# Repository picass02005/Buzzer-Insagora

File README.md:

# General description

This project is a request from Insagora club, realised in associon with Club Robot and Club Info.

It consists of a set of buzzers (ESP-32 based) communicating with a PC backend and a web frontend.

# Contacts

Club Info: <[club.info@amicale-insat.fr](mailto:club.info@amicale-insat.fr)><br>
Club Robot: <[club.robot@amicale-insat.fr](mailto:club.robot@amicale-insat.fr)>

Main developper: Clément Duran <[clementduran0@gmail.com](mailto:clementduran0@gmail.com)>

# Manual

## Software installation

### From pre-compiled code

A GitHub action is set up to compile the code on every push on `master`.

To download it:

1. Go to [actions](https://github.com/picass02005/Buzzer-Insagora/actions) tab
2. Select the last run
3. You can download an executable from artifacts (one for Windows, one for Linux)

> [!NOTE] Antivirus
> For an unknown reason, on Windows, sometimes Windows defender will block the execution.
> You can force it on the popup that will appear.

### From source code

#### Clone this project

To clone this project, you can use the following :

```bash
git clone https://github.com/picass02005/Buzzer-Insagora.git
```

#### Create a virtualenv (recommended)

To execute this code cleanly, I recommend you to create a virtualenv.
You can do this by running the following command on this project root (where this README is located):

```bash
python3 -m venv .venv
```

Then you need to load your venv environment:

```bash
# On linux
source .venv/bin/activate

# On windows
.venv\Scripts\activate.bat
```

#### Install depedencies

To install depedencies, you must run the following:

```bash
python3 -m pip -r requirements.txt
```

#### Run the program

Finally, you can run the program (you need to be at the root of this project):

```bash
python3 backend/main.py
```

#### Compile from sources

If you want to compile your own binaries, you need to install [PyInstaller](https://pyinstaller.org/en/stable/):

```bash
# This may depends on your operating system, please refer to PyInstaller documentation
python3 -m pip install pyinstaller
```

You can now compile your binary using:

```bass
make exe_win    # You must be on Windows to run this
make exe_linux  # You must be on linux to run this
```

The executable will be in `./dist`.

If needed, you have serveral tools in this project `Makefile` that you can use to compile or upload the onboard code for
ESP32 boards. Those tools uses `arduino-cli` and were tested on Linux. You can also upload it using Arduino IDE.

# Technical specifications

## Hardware

### Electronic

All files related to PCB conceptions can be found under [CAO/PCB](./CAO/PCB).

You can ask GEI for custom PCB. You need to give them the files under [pdf_mask](./CAO/PCB/pdf_mask/).

If needed, the kicad project can be found under [kicad_project](./CAO/PCB/kicad_project/).

### Casing

The casing was made using onshape. Its project can be found under [this link](https://cad.onshape.com/documents/d32b5483efb85fc275e8530b/w/3e110ba059403e44c50f27c8/e/61eb53e4b49d77882c064105?renderMode=0&uiState=69906051c49d80537d0f6ebd).

You can find all STL files necessary to 3D print it under [3D-model-str](./CAO/3D-model-stl/).

## Software

### Communication diagram

```mermaid
flowchart LR
    A[Computer] <-->|Bluetooth Low Energy| B[Buzzer-1<br>&quot;Gateway&quot;]
    subgraph Buzzer network
        B <-->|ESP-Now| C[Buzzer-2]
        B <-->|ESP-Now| D[Buzzer-3]
        B <-->|ESP-Now| E[...]
    end
```

### Computer to gateway communication

All packets sent from the computer follow the same general PDU:

```mermaid
packet
0-6: "Destination adress"
7: "ID"
8-31: "Command (separated from data by a space, variable length)"
32-63: "Data (Optional, variable length)"
64-95: "Padding (Optional, total length is 240 bytes)"
```

Data are raw bytes.
Broadcast address is `\xFF\xFF\xFF\xFF\xFF\xFF` (or more human-readable `ff:ff:ff:ff:ff:ff`).

ID refers to a command ID, used for polling responses in backend.

### Gateway to computer communication

Communication from gateway to computer isn't totally normalized.

```mermaid
packet
0: "ID"
1-31: "Data (not normalized, variable length)"
```

Max data size is 240 bytes.

It is made from `data` field of a `ESPNowMessage` where `fwd_ble` is `1`.

### Between multiple ESP

All packets through the ESP-NOW network are currently sent to broadcast address (`ff:ff:ff:ff:ff:ff`).

Each of them is a `ESPNowMessage`.

Structure of `ESPNowMessage`:

- `char fwd_ble`: Represent if the message should be forwarded through BLE network when it reaches the gateway.<br>
  To forward it, set its value to `1`, else set it to `0`.
- `char target[6]`: Contain the target ESP MAC address for this packet.<br>
  Set it to `{0xff, 0xff, 0xff, 0xff, 0xff, 0xff}` for a broadcast message.<br>
  For this purpose, you can use the `broadcastAddress` constant.
- `char data[240]`: The raw data of this packet.<br>
  If you're sending a command and its data, separate them with a space.

### Example communication

In the following example, we suppose we have a generic `PING` command where respond is in the form
`PONG [destination MAC address]`.

#### Example 1: direct command to gateway

```mermaid
sequenceDiagram
    participant C as Computer
    box Grey ESP-NOW network
        participant G as Buzzer 1 (Gateway)<br>aa:aa:aa:aa:aa:aa
        participant B2 as Buzzer 2<br>bb:bb:bb:bb:bb:bb
        participant B3 as Buzzer 3<br>cc:cc:cc:cc:cc:cc
    end

    C->>G: Target: aa:aa:aa:aa:aa:aa<br>Data: PING
    activate G
    G->>C: Data: PONG aa:aa:aa:aa:aa:aa
    deactivate G
```

#### Example 2: command to a specific buzzer

```mermaid
sequenceDiagram
    participant C as Computer
    box Grey ESP-NOW network
        participant G as Buzzer 1 (Gateway)<br>aa:aa:aa:aa:aa:aa
        participant B2 as Buzzer 2<br>bb:bb:bb:bb:bb:bb
        participant B3 as Buzzer 3<br>cc:cc:cc:cc:cc:cc
    end

    C->>G: Target: bb:bb:bb:bb:bb:bb<br>Data: PING
    G->>B2: Target: bb:bb:bb:bb:bb:bb<br>Data: PING<br>Fwd_ble: 0
    activate B2
    B2->>G: Target: aa:aa:aa:aa:aa:aa<br>Data: PONG bb:bb:bb:bb:bb:bb<br>Fwd_ble: 1
    deactivate B2
    G->>C: Data: PONG bb:bb:bb:bb:bb:bb
```

#### Example 3: command to every buzzers

```mermaid
sequenceDiagram
    participant C as Computer
    box Grey ESP-NOW network
        participant G as Buzzer 1 (Gateway)<br>aa:aa:aa:aa:aa:aa
        participant B2 as Buzzer 2<br>bb:bb:bb:bb:bb:bb
        participant B3 as Buzzer 3<br>cc:cc:cc:cc:cc:cc
    end
    
    C->>G: Target: ff:ff:ff:ff:ff:ff<br>Data: PING
    activate G
    par BROADCASTING
        G->>C: Data: PONG aa:aa:aa:aa:aa:aa
        deactivate G
        G->>B2: Target: ff:ff:ff:ff:ff:ff<br>Data: PING<br>Fwd_ble: 0
        activate B2
        B2 ->> G: target: aa:aa:aa:aa:aa:aa<br>Data: PONG bb:bb:bb:bb:bb:bb<br>Fwd_ble: 1
        deactivate B2
        G->>C: Data: PONG bb:bb:bb:bb:bb:bb
        G->>B3: Target: ff:ff:ff:ff:ff:ff<br>Data: PING<br>Fwd_ble: 0
        activate B3
        B3 ->> G: target: aa:aa:aa:aa:aa:aa<br>Data: PONG cc:cc:cc:cc:cc:cc<br>Fwd_ble: 1
        deactivate B3
        G->>C: Data: PONG cc:cc:cc:cc:cc:cc
    end
```

### Commands

#### Ping

Command used to ping any ESP.
Response contains the target MAC address (in this example : `AA:BB:CC:DD:EE:FF`).

> Command : `PING`
> Response : `PING AA:BB:CC:DD:EE:FF`

#### Get clock

Command used to get internal clock value.
If internal clock is not set, its value will be `INT64_MAX` (9,223,372,036,854,775,807)

In this example, MAC address is `AA:BB:CC:DD:EE:FF`, its internal clock is `1234`.

> Command : `GCLK`
> Response: `GCLK AA:BB:CC:DD:EE:FF 1234`

#### Reset clock

Reset an ESP internal clock.

For the master, default value is `0`.
For another ESP, default value is `INT64_MAX` (9,223,372,036,854,775,807).

This command does not send any response.

> Command: `RCLK`

#### Set clock

Command used to set internal clock.
This command does not send any response.

The internal clock is only set if new clock value is less than actual clock value.

In this example, we set the internal clock to `1234`.

> Command: `SCLK 1234`

#### Automatic set clock

Command used to delegate the set clock procedure to the master ESP.
This will execute the following commands:

1. `RCLK` (broadcast)
2. `SCLK actual_clock` (broadcast, actual_clock being the clock of master)

The `SCLK` is repeated a number of time defined by `AUTO_SET_CLK_NB` in `cmd-clock.cpp`.

> Command: `ACLK`
> Response: `ACLK success`

#### Get LED number

This command return the number of LED installed on a buzzer.

In this example, we suppose the buzzer have 8 LEDs.

> Command: `GLED`
> Response: `GLED 8`

#### Set LED

This command set the LEDs color on a buzzer.
This command does not send any response.

Each LED color is represented on 3 bytes in raw value.

Its PDU is defined as following:

```mermaid
packet
0-5: "SLED [space]"
6: "R_1"
7: "G_1"
8: "B_1"
9: "R_2"
10: "G_2"
11: "B_2"
12-31: "Other LED color (variable length)"
```

For the next example, there is a quick reminder from extended ASCII codes:

```
ASCII -> DEC | HEX
!     -> 33  | 0x21
ÿ     -> 255 | 0xff
```

In this example, I have a buzzer with 3 LED, and I want to set them to `0xFF2121`, `0x21FF21` and `0x2121FF`. This
translate into `ÿ!!`, `!ÿ!` and `!!ÿ`.

> Command: `SLED ÿ!!!ÿ!!!ÿ`

#### Clear LED

This command turn off all LEDs on a buzzer.
This command does not send any response.

> Command: `CLED`

### On board

#### Which callback to use for communication?

For every communication (from master buzzer or other buzzers), send messages using `esp_now_send_message` (defined in
`esp-now.h`).

#### How to add a command?

If you want to add commands, you need to define a callback with this signature:

```cpp
void MyAwesomeCommand(ESPNowMessage message);
```

The message passed is the original message.
You then need to add it in `commands_handler` (`commands_handler.h`).

### Backend

The backend is defined in 2 different stack:

- Communication stack
- API stack

Communication stack is responsible for the BLE communication between the PC and master buzzer.
You can find it under `./backend/ESPCommunication`.

API stack is a layer for communicating with BLE stack. It also implements teams, LED management and flow control.
You can find it under `./GUI/API`.

Every function have a full docstring you can refer to for more informations.

### API

All API calls are defined under `http://your_hostname/api`.

#### /api/status/get_connected [GET]

Return a JSON containing connected buzzers MAC address.
By default, it uses a cache value (if valid) to reduce ping.
You can force to repopulate cache by using `/api/status/get_connected?no_cache=true`.

No parameters are set in body.

Example response:

```JSON
{
    "connected": [
        "AA:AA:AA:AA:AA:AA",
        "BB:BB:BB:BB:BB:BB"
    ]
}
```

#### /api/status/get_state [GET]

Return the current flow state of the buzzers.

Valid states are:

- `IDLE`: The buzzer system is waiting for an operation. Its LED show current team points.
- `WAIT`: The buzzer system is waiting for a button press. Its LED are set to white.<br>
  When a press is registered, next state is `CHECK`.
- `CHECK`: The buzzer system is waiting for a confirmation or a denial from the game master. When waiting for
  confirmation, LEDs are green and red.<br>
  When answer is confirmed, a quick animation shows and state is set to `IDLE`.

No parameters are set in body.

Example response:

```JSON
{
    "state": "IDLE"
}
```

#### /api/flow/wait_press [POST]

Executes the following:

1. Reset master buzzer clock
2. Auto-synchronize all buzzers clock (`ACLK`)
3. Change game state to `WAIT` (+ change LED accordingly)
4. Wait for a button press event
5. Wait a few millisecond and detect the first press (regarding clock)
6. Change game state to `CHECK` (+ change LED accordingly)

No parameters are set in body.

This method return a partial file for each game state changes.

When going to `WAIT` state:

```JSON
{
    "state": "waiting for press"
}
```

When going to `CHECK` state:

```JSON
{
    "state": "waiting for confirmation"
}
```

#### /api/flow/confirm [POST]

This method must be called when in `CHECK` state to confirm a participant answer.

This makes the LED blink briefly in green and add a point to this buzzer's team.
After this method, game state go into `IDLE`.

No parameters are set in body.

This returns a JSON containing status / error like this:

```JSON
{
    "status": "ok"
}
```

#### /api/flow/deny [POST]

This method must be called when in `CHECK` state to not confirm a participant answer.

This makes the LED blink briefly in red.
After this method, game state go into `IDLE`.

No parameters are set in body.

This returns a JSON containing status / error like this:

```JSON
{
    "status": "ok"
}
```

#### /api/teams/get [GET]

This method is used to get all teams information.

No parameters are set in body.

An example return is like this:

```JSON
{
    "test_1": {
        "associated_buzzers": [
            "AA:AA:AA:AA:AA:AA"
        ],
        "name": "test_1",
        "point": 0,
        "point_limit": 8,
        "primary_color": "FF0000",
        "secondary_color": "FFFF00"
    },
    "test_2": {
        "associated_buzzers": [
            "BB:BB:BB:BB:BB:BB"
        ],
        "name": "test_2",
        "point": 0,
        "point_limit": 8,
        "primary_color": "0000FF",
        "secondary_color": "8000FF"
    }
}
```

#### /api/teams/make [POST]

This method is used to make a new team.

Your call must have the following body fields:

```JSON
{
    "team_name": "test_1",
    "primary_color": "#ff0000",
    "secondary_color": "#ffff00"
}
```

Primary color refers to the color of the team.
Secondary color is used to display points when limit is greater than 8.

This returns a JSON containing status / error like this:

```JSON
{
    "status": "ok"
}
```

#### /api/teams/delete [DELETE]

This method deletes a team.

Your call must have the following body fields:

```JSON
{
    "team_name": "test_1"
}
```

This returns a JSON containing status / error like this:

```JSON
{
    "status": "ok"
}
```

#### /api/teams/set_point_limit [PATCH]

This method set a new point limit for all teams.

After calling this method, you should reset point number.

Your call must have the following body fields:

```JSON
{
    "limit": 10
}
```

This returns a JSON containing status / error like this:

```JSON
{
    "status": "ok"
}
```

#### /api/teams/reset_points [PATCH]

This method reset all teams point to 0. After that, it reset LED display to default.

No parameters are set in body.

This returns a JSON containing status / error like this:

```JSON
{
    "status": "ok"
}
```

#### /api/teams/change_name [PATCH]

This method is used to change a team name.

Your call must have the following body fields:

```JSON
{
    "old_name": "test_1",
    "new_name": "t_1"
}
```

This returns a JSON containing status / error like this:

```JSON
{
    "status": "ok"
}
```

#### /api/teams/update [PATCH]

This method is used to update a team attributes.

Your call must define at least this body fields:

```JSON
{
    "team_name": "test_1"
}
```

You can add optional fields to modify this team attributes.

- `"associated_buzzers": ["AA:AA:AA:AA:AA:AA"]`: A list of all associated buzzers MAC addressù
- `"point": 0`: Set point number to the given value
- `"primary_color": "0000FF"`: Set the team primary color
- `"secondary_color": "00FF00"`: Set the secondary color

If you change `associated_buzzers`, backend will check that your buzzers are currently connected.

Example body:

```JSON
{
    "team_name": "test_1",
    "associated_buzzers": [
        "AA:AA:AA:AA:AA:AA"
    ],
    "point": 0,
    "primary_color": "0000FF",
    "secondary_color": "00FF00"
}
```

This returns a JSON containing status / error like this:

```JSON
{
    "status": "ok"
}
```

#### /api/lights/reset_led_default [PUT]

This method reset all buzzers LED to default value.

If status is `IDLE`, default value is the number of points lit up with team color.

If status is `WAIT`, default value is all LED in white.

If status is `CHECK`, default value is all buzzers off except the first one to have pressed the buzzer. Its LED are red
and green.

No parameters are set in body.

This returns a JSON containing status / error like this:

```JSON
{
    "status": "ok"
}
```

#### /api/lights/clear_leds [PUT]

This method set all buzzers LED to an off state.

Your call must have the following body fields:

```JSON
{
    "target_mac": "AA:AA:AA:AA:AA:AA"
}
```

This returns a JSON containing status / error like this:

```JSON
{
    "status": "ok"
}
```

#### /api/lights/get_led_nb [GET]

This method is used to get the number of onboard LED for every buzzers.

No parameters are set in body.

An example return is like this:

```JSON
{
    "number": 16
}
```

#### /api/lights/set_led_color [PUT]

This method is used to set LED color on a given buzzer, or every buzzer.

If no target MAC address is given, it defaults to broadcast address (`FF:FF:FF:FF:FF:FF`)

Example body:

```JSON
{
    "target_mac": "ff:ff:ff:ff:ff:ff",
    "colors": [
        "FF0000",
        "FFFF00",
        "00FF00",
        "00FFFF",
        "0000FF",
        "FF0000",
        "FFFF00",
        "00FF00",
        "00FFFF",
        "0000FF",
        "FF0000",
        "FFFF00",
        "00FF00",
        "00FFFF",
        "0000FF",
        "FF0000"
    ]
}
```

This returns a JSON containing status / error like this:

```JSON
{
    "status": "ok"
}
```

### Frontend

The frontend was vibe-coded using [Antigravity](https://antigravity.google/) with [Gemini](https://gemini.google.com/)
model.

One side project could be to code it properly, but by lack of time, I could not do it for now.

# License

This project is distribued under the MIT license.
For more information: https://opensource.org/licenses/MIT

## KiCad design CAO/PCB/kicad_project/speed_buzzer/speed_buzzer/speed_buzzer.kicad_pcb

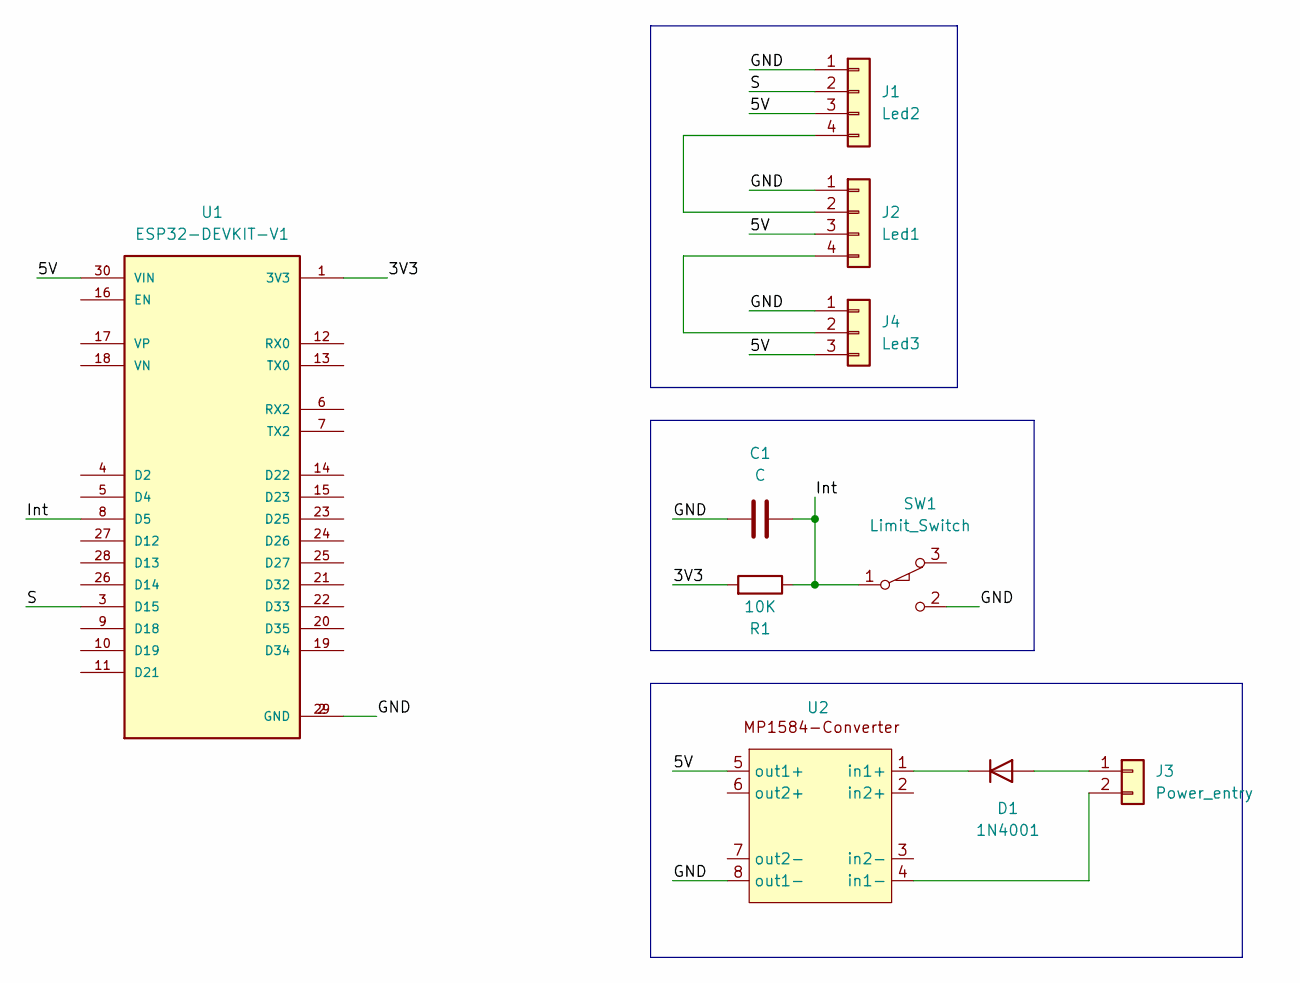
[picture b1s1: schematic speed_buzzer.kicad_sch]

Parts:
C1: C; C_Disc_D7.5mm_W2.5mm_P5.00mm
D1: 1N4001; D_DO-41_SOD81_P10.16mm_Horizontal
J1: Led2; JST_EH_B4B-EH-A_1x04_P2.50mm_Vertical
J2: Led1; JST_EH_B4B-EH-A_1x04_P2.50mm_Vertical
J3: Power_entry; JST_EH_B2B-EH-A_1x02_P2.50mm_Vertical
J4: Led3; JST_EH_B3B-EH-A_1x03_P2.50mm_Vertical
R1: 10K; R_Axial_DIN0207_L6.3mm_D2.5mm_P10.16mm_Horizontal
SW1: Limit_Switch
U1: ESP32-DEVKIT-V1; ESP32_DEVKIT_V1; PARTREV N/A
U2: mp1584

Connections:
/3V3: R1.2, U1.1 (3V3)
/5V: J1.3, J2.3, J4.3, U1.30 (VIN), U2.5 (out1+)
/GND: C1.1, J1.1, J2.1, J4.1, SW1.2 (B), U1.2 (GND), U1.29 (GND), U2.8 (out1-)
/Int: C1.2, R1.1, SW1.1 (A), U1.8 (D5)
/S: J1.2, U1.3 (D15)
unnamed: D1.2 (A), J3.1
unnamed: D1.1 (K), U2.1 (in1+)
unnamed: J1.4, J2.2
unnamed: J2.4, J4.2
unnamed: J3.2, U2.4 (in1-)

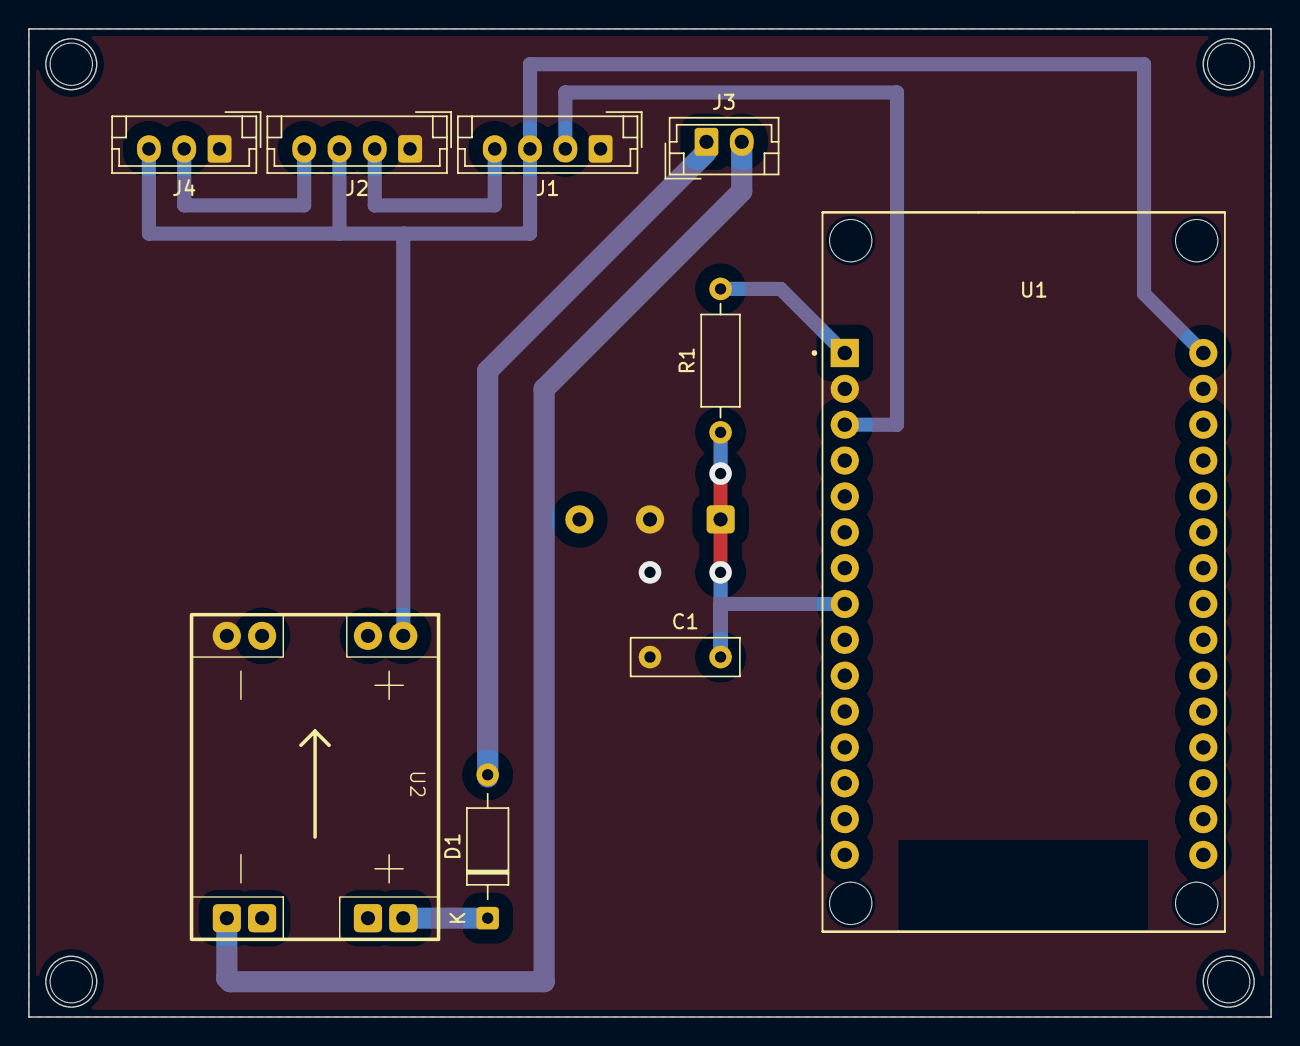
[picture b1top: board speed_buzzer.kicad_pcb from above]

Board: 2 copper layers, 88.0 x 70.0 mm, 10 parts (1 on the bottom side), 10 nets.

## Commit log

2025-11-23 Moved manual before technical specs
2025-11-23 Added license
2025-11-25 Added makefile to compile / upload ESP code
2025-11-27 Added ESP connection by BT + master detection
2025-11-28 Moved network into ble + changed BLE lib used
2025-11-28 Added esp-now connection
2025-12-04 Fixed BLE connection
2025-12-04 Added a test of ESP-NOW communication based on BLE
2025-12-05 Renamed params into data in ESP messages
2025-12-06 BLE packets are retransmissed on ESP-NOW if target != mac addr
2025-12-06 Added broadcast as valid target
2025-12-07 Added function to send BLE packets + automatic forward of BLE packets if fwd_ble=1
2025-12-07 Avoid not necessary stack copy of messages + changed data length
2025-12-07 Added generic sequence diagram to explain network
2025-12-07 Renamed BUZZERS into BUZZERS-INSAGORA
2025-12-07 Changing box to grey
2025-12-09 Added debug define to activate / desactivate serial
2025-12-09 Added command manager + PING
2025-12-11 Renamed commands into command-handler + moved ping command
2025-12-12 Added LED commands and support + fixed a bug with null bytes in BLE
2025-12-12 Changed pinout for V2 + some minor modifications with LED
2025-12-12 Minor changes
2025-12-14 Added a little LED animation over BLE
2025-12-14 Added clock managment + commands to reset, set, get and automatically set clock among clients
2025-12-15 Improved clock sync
2025-12-15 Added button interrupt
2025-12-15 Formatted every ESP files
2025-12-15 Added license headers in every files + in readme
2025-12-18 Updated readme + some commands responses
2025-12-20 Changed pin layout for prototype V3
2025-12-20 Reformated ESP code
2025-12-20 Updated gitignore
2025-12-21 Added BT communication for backend
2025-12-21 Changed data packet to include an ID for each commands
2025-12-21 Modofoed gitignore
2025-12-21 Modified readme according to new packets format
2025-12-21 Added command ID in communication
2025-12-21 WIP: ping command TODO: polling of responses
2025-12-22 Add response polling + finished ping command
2025-12-22 Updated a mermaid diagram in readme
2025-12-22 Added requirements.txt
2025-12-22 Added GCLK command + pretty format for RecvObject
2025-12-22 Added reset_clock set_clock and automatic_set_clock
2025-12-22 Added get_led_number + renamed args into data in RecvObject
2025-12-23 Added set led command, LEDs class and Color class
2025-12-23 Added clear LED command
2025-12-23 Updated TODO
2025-12-23 Add command to remove every instance of a command from polling
2025-12-23 Rewrite all docstrings using Google styling
2025-12-28 Added callback on BPRS (for now it only prints BPRS sorted by internal clock values after a short polling) + renamed "Modules" into "ESPCommunication" for later scalability
2025-12-28 Added a method to wait for a press and get only first one
2025-12-28 Using low level asyncio to run main loop forever
2025-12-28 Added GUI support + test page
2025-12-28 Added docstring + support for bt_comm in blueprints
2025-12-28 Added function to try to connect to buzzers until it's successful
2025-12-28 Added copyright + handled an exception when connecting to BLE
2026-01-04 Added majority of backend's logic
2026-01-04 Added a cache to keep a list of connected buzzers
2026-01-04 Removed some junk in main
2026-01-04 Added caching of connected buzzers + API endpoints to get status from the backend
2026-01-05 Added check API endpoint
2026-01-05 Added docstrings
2026-01-12 Added make_team endpoint + moved get_teams endpoint
2026-01-15 When ble disconnects, LEDs are reset on every ESP
2026-01-15 Added delete team
2026-01-15 Added change team name
2026-01-15 Bugfix when getting a color from hex
2026-01-15 Added update team
2026-01-15 Enhanced logic for checking if a hex value is a valid color
2026-01-15 Added docstring
2026-01-15 Added endpoint to reset LED to current state
2026-01-24 Added lights
2026-01-24 Added flow API + deleted test
2026-01-29 Modified main loop to properly propagate signals
2026-01-29 Updated README with all API doc + fixed some minor bugs
2026-01-29 Vibe coding the frontend
2026-01-29 Added a way to open main page on startup
2026-01-29 Added a default behavior when no buzzers are connected and pinging
2026-01-29 Added a refresh buzzer list button when adding / editing teams
2026-01-29 Trying to add workflow for auto build
2026-01-29 Reverting
2026-02-03 Hopefully fixed team synchronization across multiple modules
2026-02-05 Final fix
2026-02-08 Added __init__ to allow for compiling using pyinstaller + added compile commands in makefile + updated gitignore + tried github actions to compile automatically
2026-02-08 Fixed a bug in action for linux build
2026-02-08 Forgot to install pyinstaller in my action
2026-02-08 Hopefully this time is the one
2026-02-08 Updated readme + added copyright when needed
2026-02-09 Fixed makefile
2026-02-10 MAde confirm / deny animation shorter
2026-02-10 Added infinite points
2026-02-14 Trying to fix github linux build
2026-02-14 Take 2
2026-02-14 Take 3
2026-02-14 Take 4
2026-02-14 Take 5
2026-02-14 Take 6
2026-02-14 Take 7
2026-02-14 Take 8
2026-02-14 Fixed infinite point limit LED
2026-02-16 Added CAO files + updated readme accordingly

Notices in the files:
README.md:
License:
This project is distribued under the MIT license.
For more information: https://opensource.org/licenses/MIT
